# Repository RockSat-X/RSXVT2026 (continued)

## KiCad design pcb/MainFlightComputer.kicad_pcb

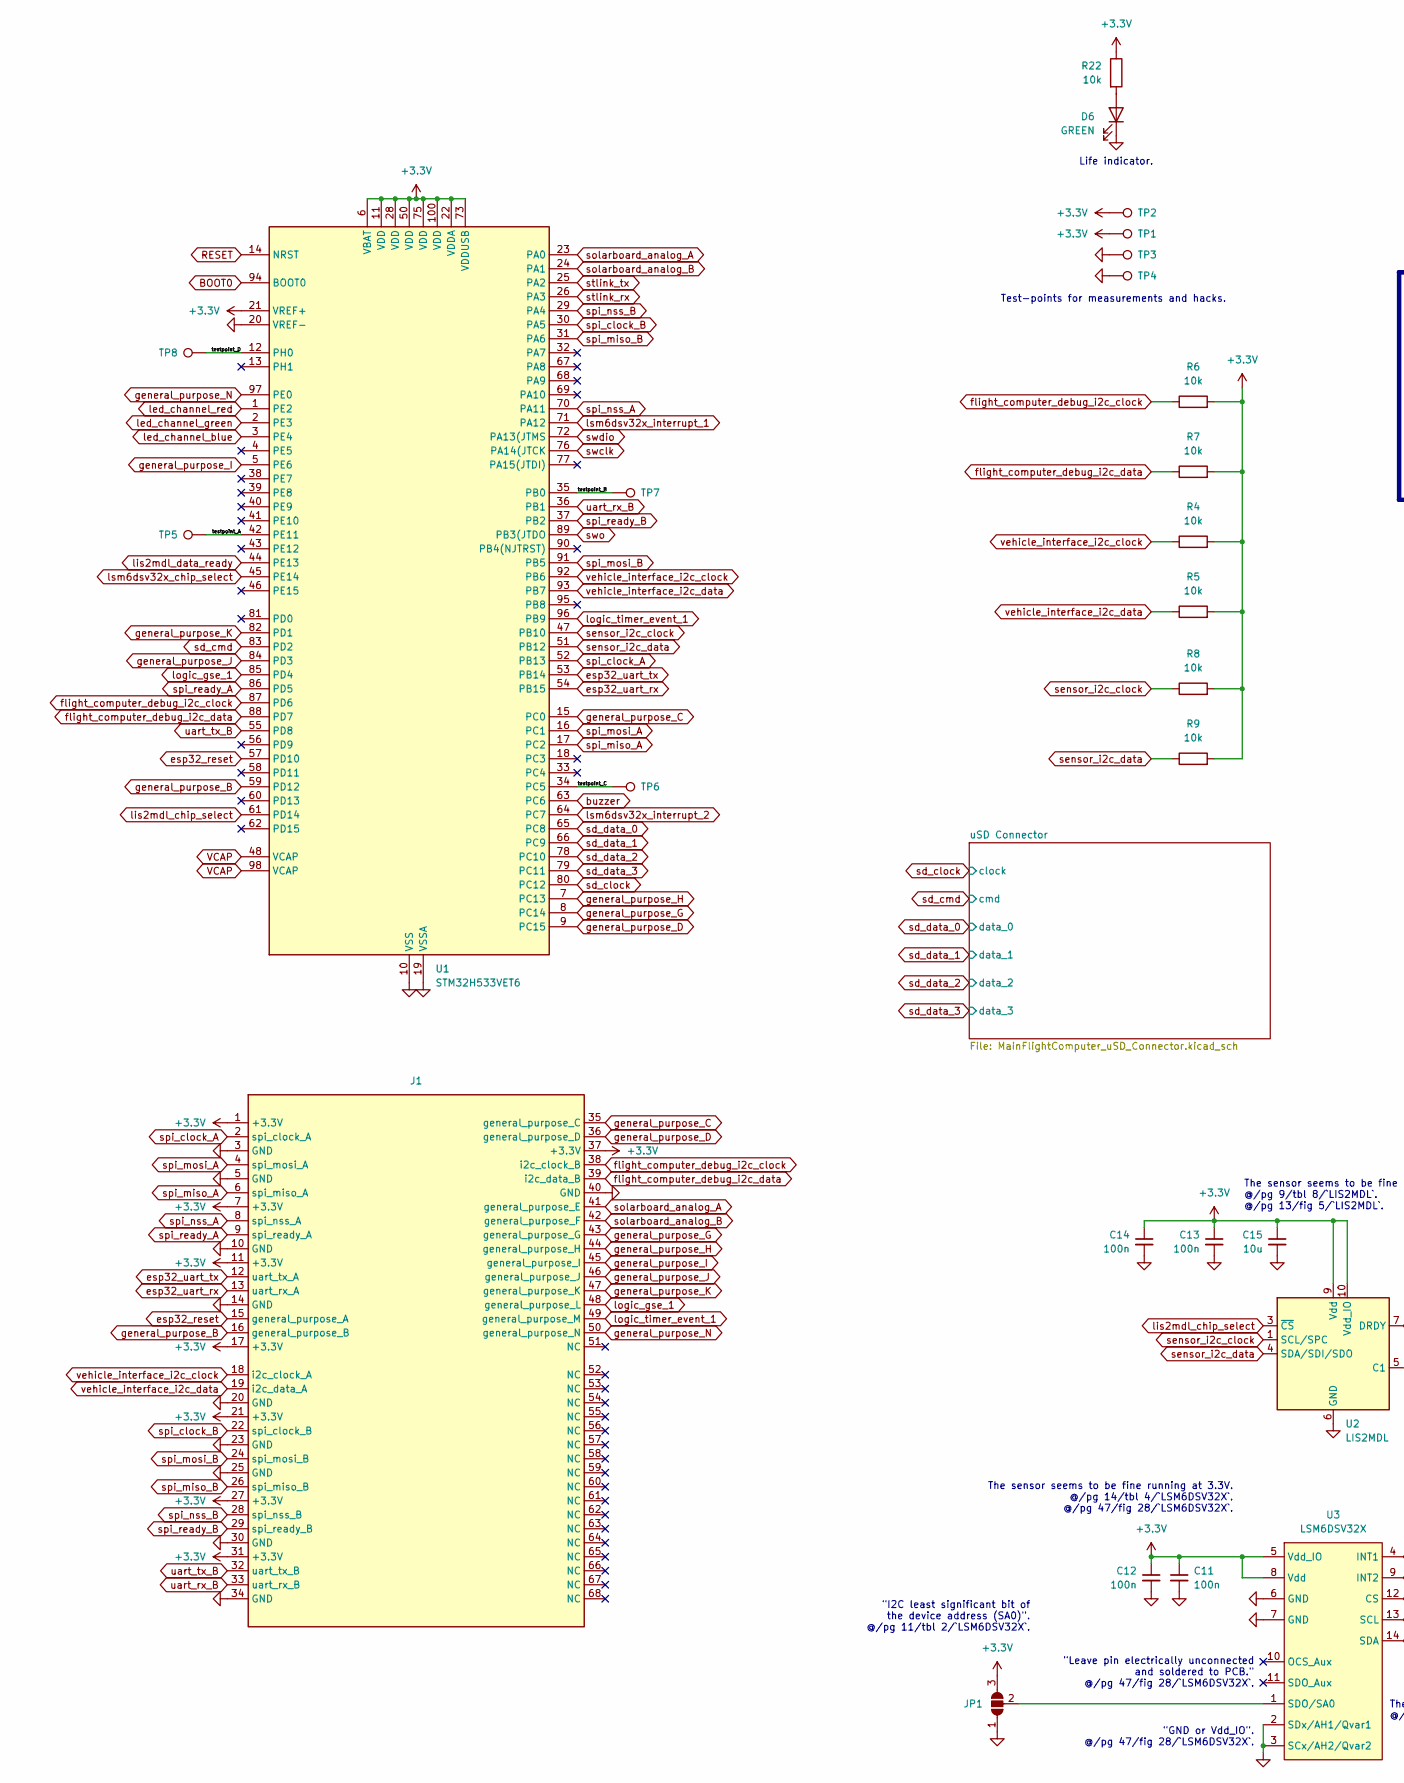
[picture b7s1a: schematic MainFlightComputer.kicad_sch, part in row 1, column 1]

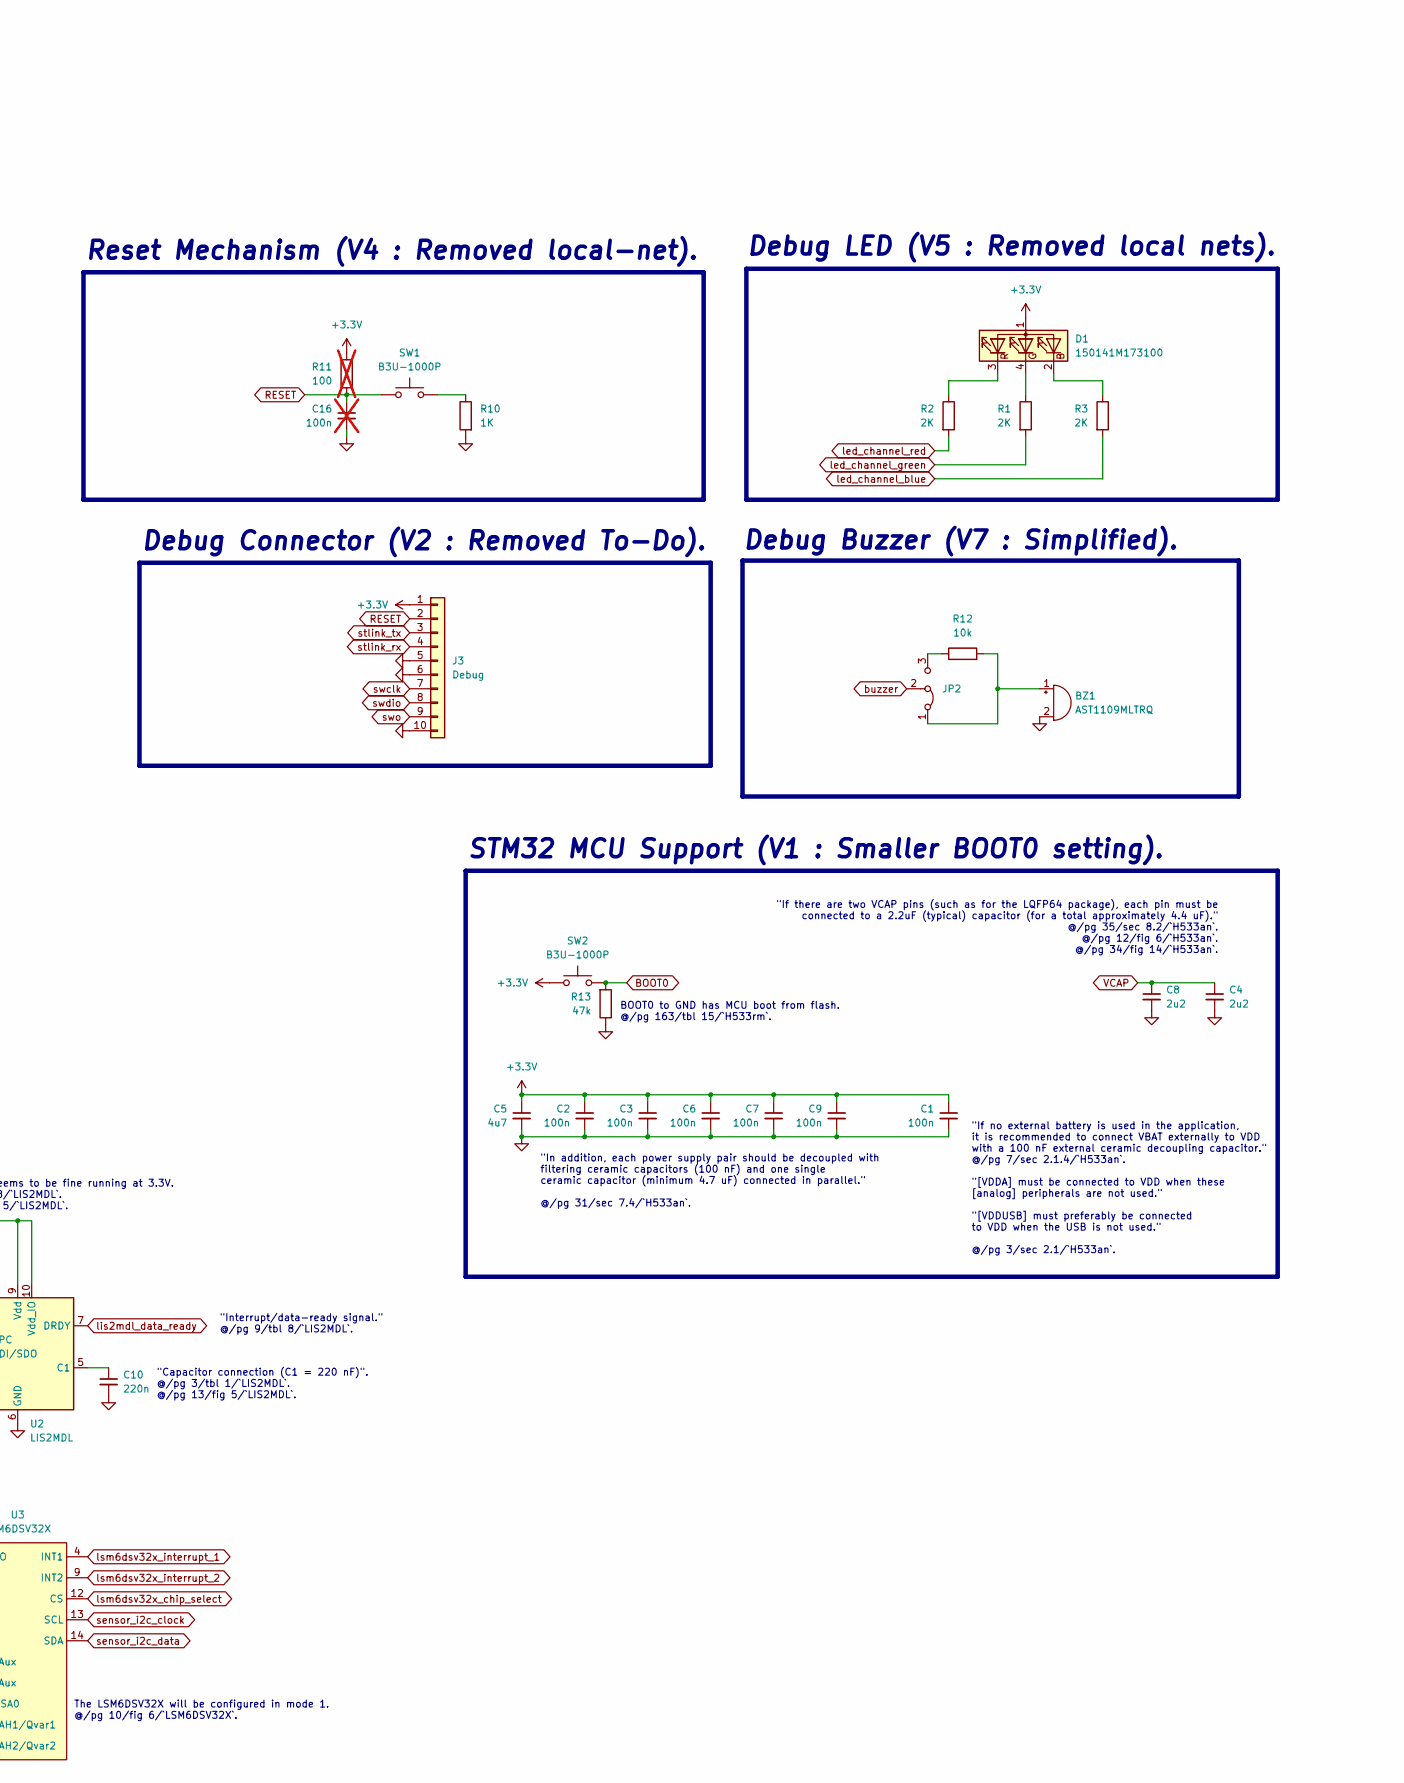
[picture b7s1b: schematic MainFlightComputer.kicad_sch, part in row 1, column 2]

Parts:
BZ1: AST1109MLTRQ; Buzzer_Mallory_AST1109MLTRQ
C1, C2, C3, C6, C7, C9, C11, C12, C13, C14: 100n; C_1206_3216Metric_Pad1.33x1.80mm_HandSolder
C4, C8: 2u2; C_1206_3216Metric_Pad1.33x1.80mm_HandSolder
C5: 4u7; C_1206_3216Metric_Pad1.33x1.80mm_HandSolder
C10: 220n; C_1206_3216Metric_Pad1.33x1.80mm_HandSolder
C15: 10u; C_1206_3216Metric_Pad1.33x1.80mm_HandSolder
C16: 100n; C_1206_3216Metric_Pad1.33x1.80mm_HandSolder; not fitted
D1: 150141M173100; LED_RGB_Wuerth-PLCC4_3.2x2.8mm_150141M173100
D6: GREEN; LED_1206_3216Metric_Pad1.42x1.75mm_HandSolder
J1: MainStackConnector
J3: Debug; Molex_PicoBlade_53047-1010_1x10_P1.25mm_Vertical
JP1: SolderJumper_3_Open; SolderJumper-3_P1.3mm_Open_RoundedPad1.0x1.5mm_NumberLabels
JP2: Jumper_3_Bridged12; PinHeader_1x03_P2.54mm_Vertical
R1, R2, R3: 2K; R_1206_3216Metric_Pad1.30x1.75mm_HandSolder
R4, R5, R6, R7, R8, R9, R12, R22: 10k; R_1206_3216Metric_Pad1.30x1.75mm_HandSolder
R10: 1K; R_1206_3216Metric_Pad1.30x1.75mm_HandSolder
R11: 100; R_1206_3216Metric_Pad1.30x1.75mm_HandSolder; not fitted
R13: 47k; R_1206_3216Metric_Pad1.30x1.75mm_HandSolder
SW1, SW2: B3U-1000P; SW_SPST_B3U-1000P
TP1, TP2, TP3, TP4, TP5, TP6, TP7, TP8: TestPoint; TestPoint_Bridge_Pitch2.0mm_Drill0.7mm
U1: STM32H533VET6; LQFP-100_14x14mm_P0.5mm
U2: LIS2MDL; LGA-12_2x2mm_P0.5mm
U3: LSM6DSV32X; LGA-14_3x2.5mm_P0.5mm_LayoutBorder3x4y

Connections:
+3.3V: C1.1, C2.1, C3.1, C5.1, C6.1, C7.1, C9.1, C11.1, C12.1, C13.1, C14.1, C15.1, D1.1 (A), J1.1 (+3.3V), J1.7 (+3.3V), J1.11 (+3.3V), J1.17 (+3.3V), J1.21 (+3.3V), J1.27 (+3.3V), J1.31 (+3.3V), J1.37 (+3.3V), J3.1, JP1.3 (B), R4.2, R5.2, R6.2, R7.2, R8.2, R9.2, R11.1, R22.1, SW2.1, TP1.1, TP2.1, U1.6 (VBAT), U1.11 (VDD), U1.21 (VREF+), U1.22 (VDDA), U1.28 (VDD), U1.50 (VDD), U1.73 (VDDUSB), U1.75 (VDD), U1.100 (VDD), U2.9 (Vdd), U2.10 (Vdd_IO), U3.5 (Vdd_IO), U3.8 (Vdd); also elsewhere on the board
/testpoint_A: TP5.1, U1.42 (PE11)
/testpoint_B: TP7.1, U1.35 (PB0)
/testpoint_C: TP6.1, U1.34 (PC5)
/testpoint_D: TP8.1, U1.12 (PH0)
BOOT0: R13.2, SW2.2, U1.94 (BOOT0)
GND: BZ1.2 (-), C1.2, C2.2, C3.2, C4.2, C5.2, C6.2, C7.2, C8.2, C9.2, C10.2, C11.2, C12.2, C13.2, C14.2, C15.2, C16.2, D6.1 (K), J1.3 (GND), J1.5 (GND), J1.10 (GND), J1.14 (GND), J1.20 (GND), J1.23 (GND), J1.25 (GND), J1.30 (GND), J1.34 (GND), J1.40 (GND), J3.5, J3.6, J3.10, JP1.1 (A), R10.2, R13.1, TP3.1, TP4.1, U1.10 (VSS), U1.19 (VSSA), U1.20 (VREF-), U1.27 (VSS), U1.49 (VSS), U1.74 (VSS), U1.99 (VSS), U2.6 (GND), U2.8 (GND), U3.2 (SDx/AH1/Qvar1), U3.3 (SCx/AH2/Qvar2), U3.6 (GND), U3.7 (GND); also elsewhere on the board
unnamed: BZ1.1 (+), JP2.1 (A), R12.2
unnamed: D1.2 (BK), R3.1
unnamed: D1.4 (GK), R1.1
unnamed: D1.3 (RK), R2.1
unnamed: D6.2 (A), R22.2
unnamed: JP1.2 (C), U3.1 (SDO/SA0)
unnamed: JP2.3 (B), R12.1
unnamed: R10.1, SW1.2
unnamed: C10.1, U2.5 (C1)
RESET: C16.1, J3.2, R11.2, SW1.1, U1.14 (NRST)
VCAP: C4.1, C8.1, U1.48 (VCAP), U1.98 (VCAP)
buzzer: JP2.2 (C), U1.63 (PC6)
esp32_reset: J1.15 (general_purpose_A), U1.57 (PD10)
esp32_uart_rx: J1.13 (uart_rx_A), U1.54 (PB15)
esp32_uart_tx: J1.12 (uart_tx_A), U1.53 (PB14)
flight_computer_debug_i2c_clock: J1.38 (i2c_clock_B), R6.1, U1.87 (PD6)
flight_computer_debug_i2c_data: J1.39 (i2c_data_B), R7.1, U1.88 (PD7)
general_purpose_B: J1.16 (general_purpose_B), U1.59 (PD12)
general_purpose_C: J1.35 (general_purpose_C), U1.15 (PC0)
general_purpose_D: J1.36 (general_purpose_D), U1.9 (PC15)
general_purpose_G: J1.43 (general_purpose_G), U1.8 (PC14)
general_purpose_H: J1.44 (general_purpose_H), U1.7 (PC13)
general_purpose_I: J1.45 (general_purpose_I), U1.5 (PE6)
general_purpose_J: J1.46 (general_purpose_J), U1.84 (PD3)
general_purpose_K: J1.47 (general_purpose_K), U1.82 (PD1)
general_purpose_N: J1.50 (general_purpose_N), U1.97 (PE0)
led_channel_blue: R3.2, U1.3 (PE4)
led_channel_green: R1.2, U1.2 (PE3)
led_channel_red: R2.2, U1.1 (PE2)
lis2mdl_chip_select: U1.61 (PD14), U2.3 (~CS)
lis2mdl_data_ready: U1.44 (PE13), U2.7 (DRDY)
logic_gse_1: J1.48 (general_purpose_L), U1.85 (PD4)
logic_timer_event_1: J1.49 (general_purpose_M), U1.96 (PB9)
lsm6dsv32x_chip_select: U1.45 (PE14), U3.12 (CS)
lsm6dsv32x_interrupt_1: U1.71 (PA12), U3.4 (INT1)
lsm6dsv32x_interrupt_2: U1.64 (PC7), U3.9 (INT2)
sd_clock: U1.80 (PC12); also elsewhere on the board
sd_cmd: U1.83 (PD2); also elsewhere on the board
sd_data_0: U1.65 (PC8); also elsewhere on the board
sd_data_1: U1.66 (PC9); also elsewhere on the board
sd_data_2: U1.78 (PC10); also elsewhere on the board
sd_data_3: U1.79 (PC11); also elsewhere on the board
sensor_i2c_clock: R8.1, U1.47 (PB10), U2.1 (SCL/SPC), U3.13 (SCL)
sensor_i2c_data: R9.1, U1.51 (PB12), U2.4 (SDA/SDI/SDO), U3.14 (SDA)
solarboard_analog_A: J1.41 (general_purpose_E), U1.23 (PA0)
solarboard_analog_B: J1.42 (general_purpose_F), U1.24 (PA1)
spi_clock_A: J1.2 (spi_clock_A), U1.52 (PB13)
spi_clock_B: J1.22 (spi_clock_B), U1.30 (PA5)
spi_miso_A: J1.6 (spi_miso_A), U1.17 (PC2)
spi_miso_B: J1.26 (spi_miso_B), U1.31 (PA6)
spi_mosi_A: J1.4 (spi_mosi_A), U1.16 (PC1)
spi_mosi_B: J1.24 (spi_mosi_B), U1.91 (PB5)
spi_nss_A: J1.8 (spi_nss_A), U1.70 (PA11)
spi_nss_B: J1.28 (spi_nss_B), U1.29 (PA4)
spi_ready_A: J1.9 (spi_ready_A), U1.86 (PD5)
spi_ready_B: J1.29 (spi_ready_B), U1.37 (PB2)
stlink_rx: J3.4, U1.26 (PA3)
stlink_tx: J3.3, U1.25 (PA2)
swclk: J3.7, U1.76 (PA14(JTCK)
swdio: J3.8, U1.72 (PA13(JTMS)
swo: J3.9, U1.89 (PB3(JTDO)
uart_rx_B: J1.33 (uart_rx_B), U1.36 (PB1)
uart_tx_B: J1.32 (uart_tx_B), U1.55 (PD8)
vehicle_interface_i2c_clock: J1.18 (i2c_clock_A), R4.1, U1.92 (PB6)
vehicle_interface_i2c_data: J1.19 (i2c_data_A), R5.1, U1.93 (PB7)

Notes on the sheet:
STM32 MCU Support (V1 : Smaller BOOT0 setting).
Life indicator.
"Interrupt/data-ready signal." @/pg 9/tbl 8/`LIS2MDL`.
Reset Mechanism (V4 : Removed local-net).
The sensor seems to be fine running at 3.3V. @/pg 14/tbl 4/`LSM6DSV32X`. @/pg 47/fig 28/`LSM6DSV32X`.
Debug Connector (V2 : Removed To-Do).
The sensor seems to be fine running at 3.3V. @/pg 9/tbl 8/`LIS2MDL`. @/pg 13/fig 5/`LIS2MDL`.
Test-points for measurements and hacks.
BOOT0 to GND has MCU boot from flash. @/pg 163/tbl 15/`H533rm`.
"GND or Vdd_IO". @/pg 47/fig 28/`LSM6DSV32X`.
"If there are two VCAP pins (such as for the LQFP64 package), each pin must be connected to a 2.2uF (typical) capacitor (for a total approximately 4.4 uF)." @/pg 35/sec 8.2/`H533an`. @/pg 12/fig 6/`H533an`. @/pg 34/fig 14/`H533an`.
The LSM6DSV32X will be configured in mode 1. @/pg 10/fig 6/`LSM6DSV32X`.
"Capacitor connection (C1 = 220 nF)". @/pg 3/tbl 1/`LIS2MDL`. @/pg 13/fig 5/`LIS2MDL`.
"Leave pin electrically unconnected and soldered to PCB." @/pg 47/fig 28/`LSM6DSV32X`.
"In addition, each power supply pair should be decoupled with filtering ceramic capacitors (100 nF) and one single ceramic capacitor (minimum 4.7 uF) connected in parallel." @/pg 31/sec 7.4/`H533an`.
"If no external battery is used in the application, it is recommended to connect VBAT externally to VDD with a 100 nF external ceramic decoupling capacitor." @/pg 7/sec 2.1.4/`H533an`. "[VDDA] must be connected to VDD when these [analog] peripherals are not used." "[VDDUSB] must preferably be conne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
Debug Buzzer (V7 : Simplified).
Debug LED (V5 : Removed local nets).
"I2C least significant bit of the device address (SA0)". @/pg 11/tbl 2/`LSM6DSV32X`.

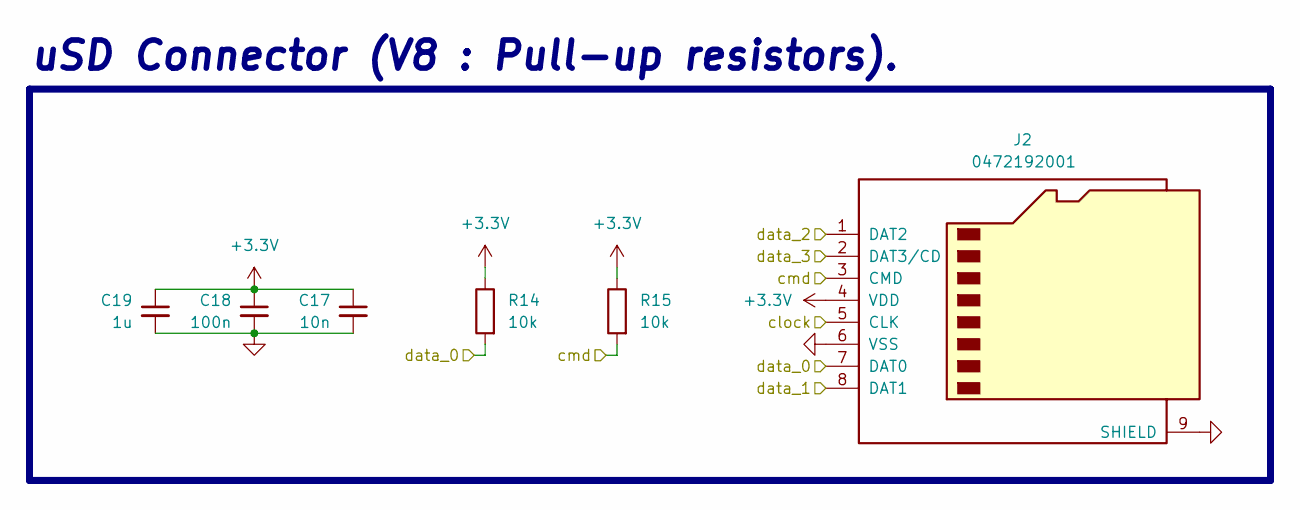
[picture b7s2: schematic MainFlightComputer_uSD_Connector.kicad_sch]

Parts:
C17: 10n; C_1206_3216Metric_Pad1.33x1.80mm_HandSolder
C18: 100n; C_1206_3216Metric_Pad1.33x1.80mm_HandSolder
C19: 1u; C_1206_3216Metric_Pad1.33x1.80mm_HandSolder
J2: 0472192001; microSD_HC_Molex_47219-2001
R14, R15: 10k; R_1206_3216Metric_Pad1.30x1.75mm_HandSolder

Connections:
+3.3V: C17.1, C18.1, C19.1, J2.4 (VDD), R14.1, R15.1; also elsewhere on the board
GND: C17.2, C18.2, C19.2, J2.6 (VSS), J2.9 (SHIELD); also elsewhere on the board
sd_clock: J2.5 (CLK); also elsewhere on the board
sd_cmd: J2.3 (CMD), R15.2; also elsewhere on the board
sd_data_0: J2.7 (DAT0), R14.2; also elsewhere on the board
sd_data_1: J2.8 (DAT1); also elsewhere on the board
sd_data_2: J2.1 (DAT2); also elsewhere on the board
sd_data_3: J2.2 (DAT3/CD); also elsewhere on the board

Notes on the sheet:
uSD Connector (V8 : Pull-up resistors).

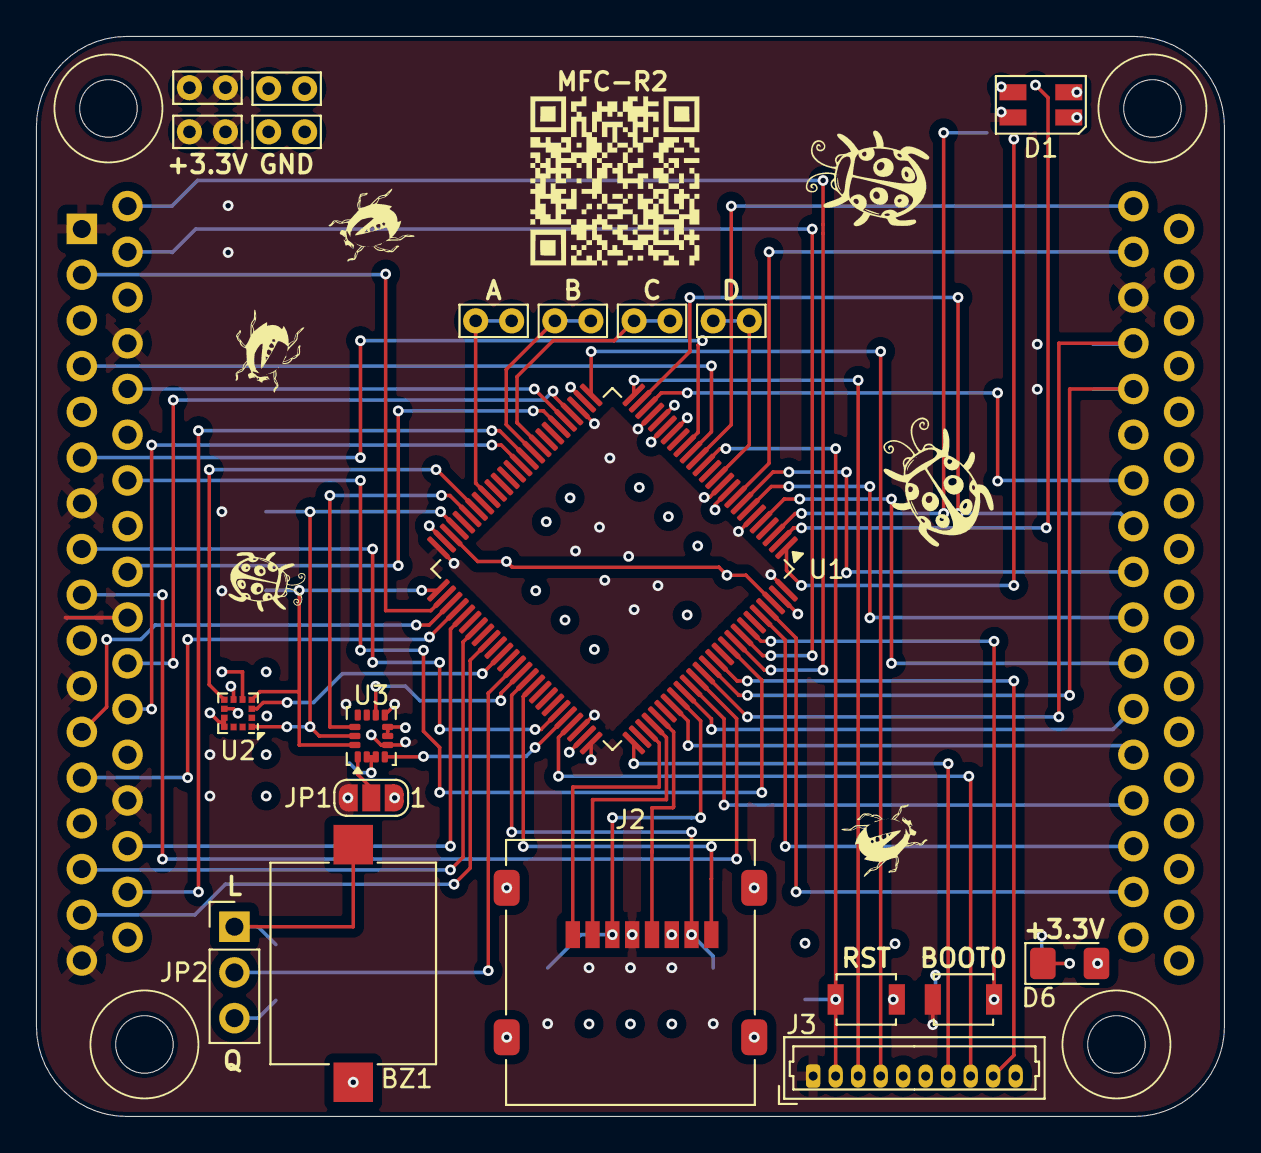
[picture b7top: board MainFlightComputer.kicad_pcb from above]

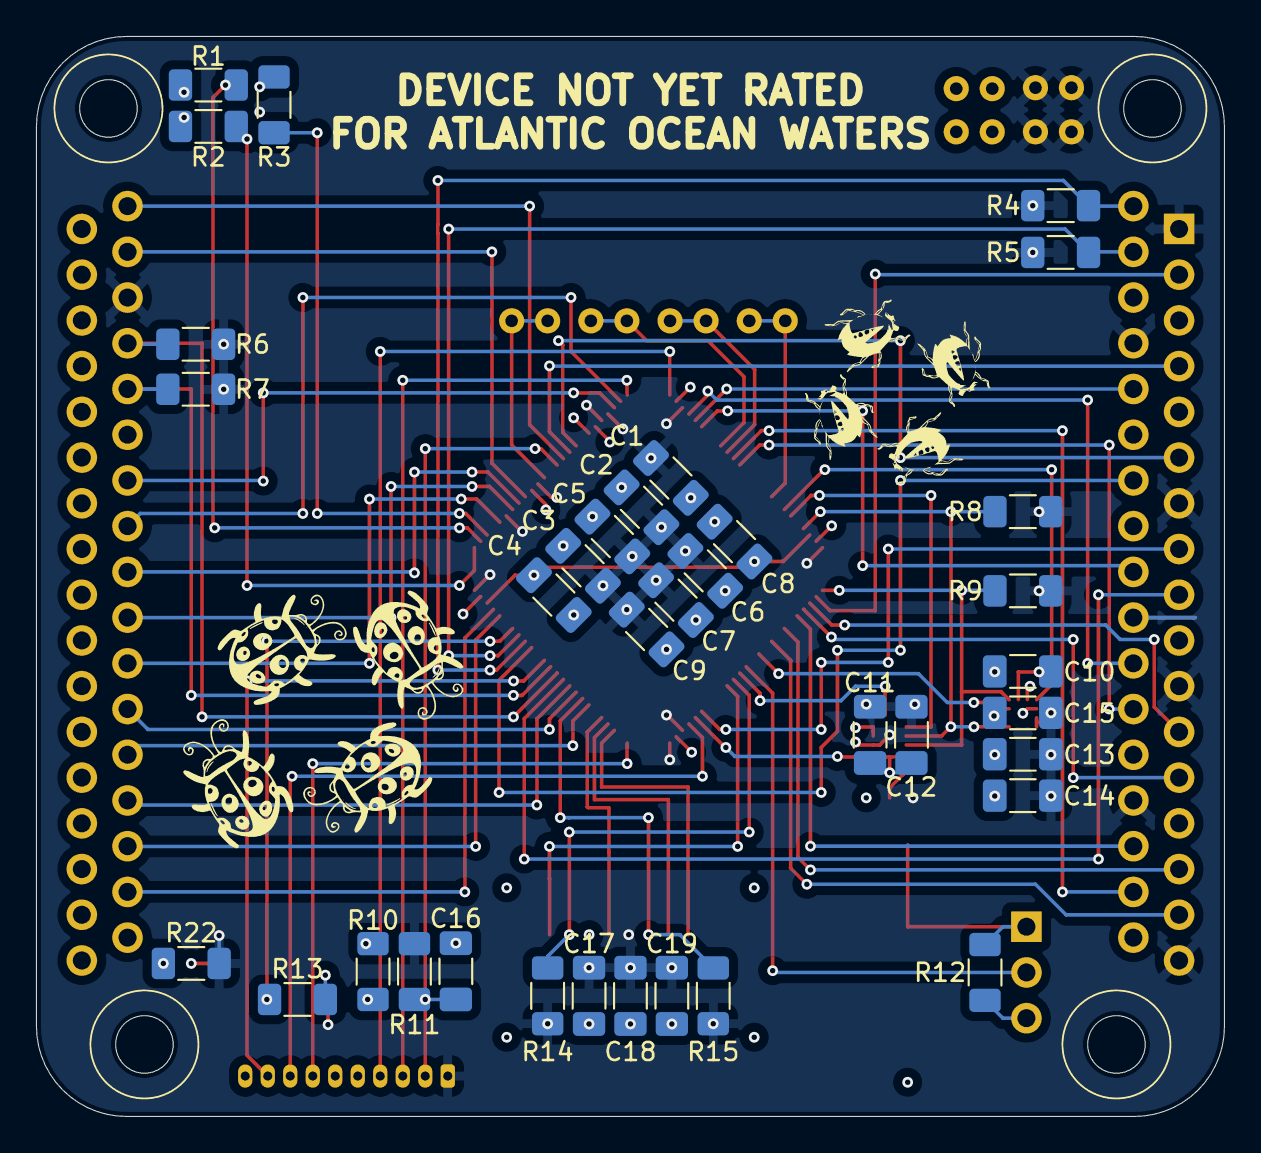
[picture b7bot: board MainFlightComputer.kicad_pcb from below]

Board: 4 copper layers, 66.0 x 60.0 mm, 57 parts (35 on the bottom side), 72 nets.

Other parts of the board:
N1: Housing; MainFlightComputerHousing

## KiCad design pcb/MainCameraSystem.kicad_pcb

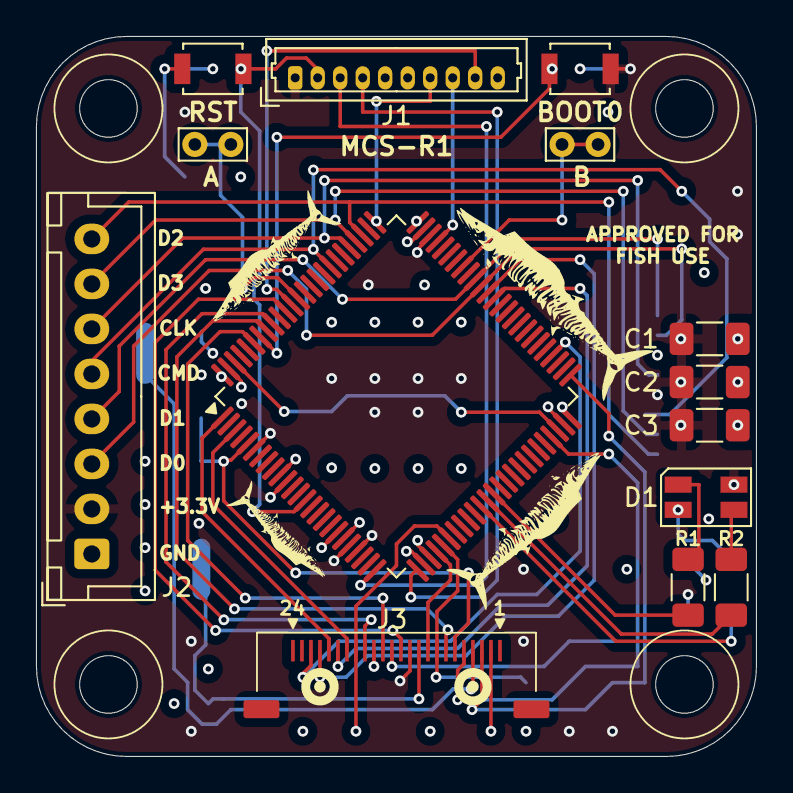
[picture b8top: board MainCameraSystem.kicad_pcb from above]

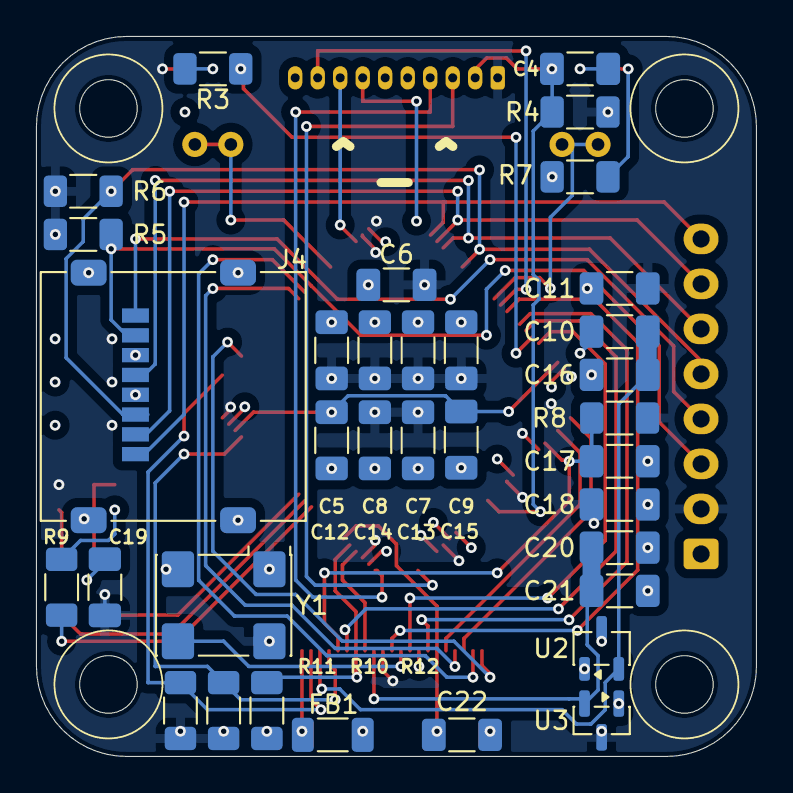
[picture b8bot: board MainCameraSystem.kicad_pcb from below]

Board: 4 copper layers, 40.0 x 40.0 mm, 52 parts (34 on the bottom side), 44 nets.

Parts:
C1, C16, C18, C20: 1u; C_1206_3216Metric_Pad1.33x1.80mm_HandSolder
C2, C4, C5, C6, C7, C8, C13, C14, C17: 100n; C_1206_3216Metric_Pad1.33x1.80mm_HandSolder
C3, C19: 10n; C_1206_3216Metric_Pad1.33x1.80mm_HandSolder
C9: 4u7; C_1206_3216Metric_Pad1.33x1.80mm_HandSolder
C10, C11, C21: 10u; C_1206_3216Metric_Pad1.33x1.80mm_HandSolder
C12, C15: 2u2; C_1206_3216Metric_Pad1.33x1.80mm_HandSolder
C22: 22p; C_1206_3216Metric_Pad1.33x1.80mm_HandSolder
D1: 150141M173100; LED_RGB_Wuerth-PLCC4_3.2x2.8mm_150141M173100
FB1: Ferrite; L_1206_3216Metric_Pad1.22x1.90mm_HandSolder
H1, H2, H3, H4: MountingHole; MountingHole_3.2mm_M3
J1: Debug; Molex_PicoBlade_53047-1010_1x10_P1.25mm_Vertical
J2: B8B-XH-A; JST_XH_B8B-XH-A_1x08_P2.50mm_Vertical
J3: XF3M_2415_1B; XF3M_2415_1B - REVERSED
J4: 0472192001; microSD_HC_Molex_47219-2001
R1, R2, R9: 2K; R_1206_3216Metric_Pad1.30x1.75mm_HandSolder
R3: 47k; R_1206_3216Metric_Pad1.30x1.75mm_HandSolder
R4: 100; R_1206_3216Metric_Pad1.30x1.75mm_HandSolder
R5, R6, R8, R10, R11, R12: 10k; R_1206_3216Metric_Pad1.30x1.75mm_HandSolder
R7: 1K; R_1206_3216Metric_Pad1.30x1.75mm_HandSolder
SW1, SW2: B3U-1000P; SW_SPST_B3U-1000P
TP1, TP2: TestPoint; TestPoint_Bridge_Pitch2.0mm_Drill0.7mm
U1: STM32H533VET6; LQFP-100_14x14mm_P0.5mm
U2: AP2127N-2.8TRG1; SOT-23-3
U3: AP2127N-1.5TRG1; SOT-23
Y1: ASV-24.000MHZ-EJ-T; Oscillator_SMD_Abracon_ASV-4Pin_7.0x5.1mm

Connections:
+1V5: C20.1, C21.1, J3.10, U3.2 (VO)
+2V8: C10.1, C16.1, J3.4, U2.2 (VO)
+3.3V: C1.1, C2.1, C3.1, C5.1, C6.1, C7.1, C8.1, C9.1, C11.1, C13.1, C14.1, C18.1, C19.1, D1.1 (A), J1.1, J2.2, J3.11, J4.4 (VDD), R4.1, R5.1, R6.1, R8.1, R10.1, R11.1, SW2.1, U1.6 (VBAT), U1.11 (VDD), U1.21 (VREF+), U1.22 (VDDA), U1.28 (VDD), U1.50 (VDD), U1.73 (VDDUSB), U1.75 (VDD), U1.100 (VDD), U2.3 (VI), U3.3 (VI), Y1.1 (EN), Y1.4 (Vdd)
/testpoint_A: TP1.1, U1.88 (PD7)
/testpoint_B: TP2.1, U1.68 (PA9)
BOOT0: R3.2, SW2.2, U1.94 (BOOT0)
GND: C1.2, C2.2, C3.2, C4.2, C5.2, C6.2, C7.2, C8.2, C9.2, C10.2, C11.2, C12.2, C13.2, C14.2, C15.2, C16.2, C17.2, C18.2, C19.2, C20.2, C21.2, C22.2, FB1.1, J1.5, J1.6, J1.10, J2.1, J3.15, J4.6 (VSS), J4.9 (SHIELD), R3.1, R7.2, R12.2, U1.10 (VSS), U1.19 (VSSA), U1.20 (VREF-), U1.27 (VSS), U1.49 (VSS), U1.74 (VSS), U1.99 (VSS), U2.1 (GND), U3.1 (GND), Y1.2 (GND)
GNDA: FB1.2, J3.2
unnamed: D1.2 (BK), R2.1
unnamed: D1.4 (GK), R9.1
unnamed: D1.3 (RK), R1.1
unnamed: R7.1, SW1.2
OV_XCLK: J3.13, Y1.3 (OUT)
RESET: C4.1, J1.2, R4.2, SW1.1, U1.14 (NRST)
VCAP: C12.1, C15.1, U1.48 (VCAP), U1.98 (VCAP)
led_channel_blue: R2.2, U1.37 (PB2)
led_channel_green: R9.2, U1.36 (PB1)
led_channel_red: R1.2, U1.38 (PE7)
ovcam_hsync: J3.9, U1.29 (PA4)
ovcam_i2c_clock: J3.5, R10.2, U1.47 (PB10)
ovcam_i2c_data: J3.3, R11.2, U1.51 (PB12)
ovcam_pixel_clock: C22.1, J3.17, U1.31 (PA6)
ovcam_power_down: J3.8, R12.1, U1.30 (PA5)
ovcam_reset: C17.1, J3.6, R8.2, U1.5 (PE6)
ovcam_vsync: J3.7, U1.93 (PB7)
ovcam_y2: J3.19, U1.63 (PC6)
ovcam_y3: J3.21, U1.64 (PC7)
ovcam_y4: J3.22, U1.54 (PB15)
ovcam_y5: J3.20, U1.1 (PE2)
ovcam_y6: J3.18, U1.3 (PE4)
ovcam_y7: J3.16, U1.92 (PB6)
ovcam_y8: J3.14, U1.95 (PB8)
ovcam_y9: J3.12, U1.90 (PB4(NJTRST))
sd_clock: J2.6, J4.5 (CLK), U1.80 (PC12)
sd_cmd: J2.5, J4.3 (CMD), R6.2, U1.83 (PD2)
sd_data_0: J2.3, J4.7 (DAT0), R5.2, U1.65 (PC8)
sd_data_1: J2.4, J4.8 (DAT1), U1.66 (PC9)
sd_data_2: J2.8, J4.1 (DAT2), U1.78 (PC10)
sd_data_3: J2.7, J4.2 (DAT3/CD), U1.79 (PC11)
stlink_rx: J1.4, U1.26 (PA3)
stlink_tx: J1.3, U1.25 (PA2)
swclk: J1.7, U1.76 (PA14(JTCK)
swdio: J1.8, U1.72 (PA13(JTMS)
swo: J1.9, U1.89 (PB3(JTDO)

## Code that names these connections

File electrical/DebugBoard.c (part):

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    for (i32 i = 0; i < 32; i += 1)
    {

        GPIO_ACTIVE  (led_channel_red_A  );
        GPIO_INACTIVE(led_channel_green_A);
        GPIO_INACTIVE(led_channel_blue_A );
        GPIO_ACTIVE  (led_channel_red_B  );
        GPIO_INACTIVE(led_channel_green_B);
        GPIO_INACTIVE(led_channel_blue_B );
        GPIO_ACTIVE  (led_channel_red_C  );
        GPIO_INACTIVE(led_channel_green_C);
        GPIO_INACTIVE(led_channel_blue_C );
        GPIO_ACTIVE  (led_channel_red_D  );
        GPIO_INACTIVE(led_channel_green_D);
        GPIO_INACTIVE(led_channel_blue_D );
        spinlock_us(50'000);

        GPIO_INACTIVE(led_channel_red_A  );
        GPIO_INACTIVE(led_channel_green_A);
        GPIO_INACTIVE(led_channel_blue_A );
        GPIO_INACTIVE(led_channel_red_B  );
        GPIO_INACTIVE(led_channel_green_B);
        GPIO_INACTIVE(led_channel_blue_B );
        GPIO_INACTIVE(led_channel_red_C  );
        GPIO_INACTIVE(led_channel_green_C);
        GPIO_INACTIVE(led_channel_blue_C );
        GPIO_INACTIVE(led_channel_red_D  );
        GPIO_INACTIVE(led_channel_green_D);
        GPIO_INACTIVE(led_channel_blue_D );
        spinlock_us(50'000);

    }
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        if (havent_received_a_packet_in_a_while && !BUZZER_current_tune())
        {
            BUZZER_play(BuzzerTune_hazard);
            GPIO_TOGGLE  (led_channel_red_C  );
            GPIO_INACTIVE(led_channel_green_C);
            GPIO_INACTIVE(led_channel_blue_C );
        }


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            {
                condition = "???";

                GPIO_ACTIVE(led_channel_red_B  );
                GPIO_ACTIVE(led_channel_green_B);
                GPIO_ACTIVE(led_channel_blue_B );

            }
            else
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                BUZZER_play(BuzzerTune_deep_beep);
            }

            GPIO_ACTIVE  (led_channel_red_B  );
            GPIO_INACTIVE(led_channel_green_B);
            GPIO_INACTIVE(led_channel_blue_B );

        }
        else
        {
            GPIO_INACTIVE(led_channel_red_B  );
            GPIO_ACTIVE  (led_channel_green_B);
            GPIO_INACTIVE(led_channel_blue_B );
        }

        if (TIMEKEEPING_microseconds() - status_flag_timestamp_us >= 1'000'000) // Scroll the statuses slowly over time.
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        if (completely_wipe_filesystem)
        {
            BUZZER_play(BuzzerTune_tetris);
            GPIO_ACTIVE(led_channel_red_D  );
            GPIO_ACTIVE(led_channel_green_D);
            GPIO_ACTIVE(led_channel_blue_D );
        }
        else
        {
            GPIO_ACTIVE  (led_channel_red_D  );
            GPIO_INACTIVE(led_channel_green_D);
            GPIO_ACTIVE  (led_channel_blue_D );
        }


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
        completely_wipe_filesystem = false;

        GPIO_INACTIVE(led_channel_red_D  );
        GPIO_INACTIVE(led_channel_green_D);
        GPIO_INACTIVE(led_channel_blue_D );

        switch (reinit_result)
        {
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
            case FileSystemReinitResult_success:
            {
                GPIO_INACTIVE(led_channel_red_D  );
                GPIO_ACTIVE  (led_channel_green_D);
                GPIO_INACTIVE(led_channel_blue_D );
            } break;


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
                for (i32 i = 0; i < 32; i += 1)
                {
                    GPIO_TOGGLE  (led_channel_red_D  );
                    GPIO_INACTIVE(led_channel_green_D);
                    GPIO_TOGGLE  (led_channel_blue_D );
                    FREERTOS_delay_ms(25);
                }

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
                for (i32 i = 0; i < 128; i += 1)
                {
                    GPIO_TOGGLE(led_channel_red_D  );
                    GPIO_TOGGLE(led_channel_green_D);
                    GPIO_TOGGLE(led_channel_blue_D );
                    FREERTOS_delay_ms(25);
                }

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
                    case FileSystemSaveResult_success:
                    {
                        GPIO_INACTIVE(led_channel_red_D  );
                        GPIO_TOGGLE  (led_channel_green_D);
                        GPIO_INACTIVE(led_channel_blue_D );
                    } break;


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        while (BUZZER_current_tune())
        {

            GPIO_ACTIVE  (led_channel_red_A  );
            GPIO_INACTIVE(led_channel_green_A);
            GPIO_INACTIVE(led_channel_blue_A );
            FREERTOS_delay_ms(20);

            GPIO_ACTIVE  (led_channel_red_A  );
            GPIO_ACTIVE  (led_channel_green_A);
            GPIO_INACTIVE(led_channel_blue_A );
            FREERTOS_delay_ms(20);

            GPIO_INACTIVE(led_channel_red_A  );
            GPIO_ACTIVE  (led_channel_green_A);
            GPIO_INACTIVE(led_channel_blue_A );
            FREERTOS_delay_ms(20);

            GPIO_INACTIVE(led_channel_red_A  );
            GPIO_ACTIVE  (led_channel_green_A);
            GPIO_ACTIVE  (led_channel_blue_A );
            FREERTOS_delay_ms(20);

            GPIO_INACTIVE(led_channel_red_A  );
            GPIO_INACTIVE(led_channel_green_A);
            GPIO_ACTIVE  (led_channel_blue_A );
            FREERTOS_delay_ms(20);

            GPIO_ACTIVE  (led_channel_red_A  );
            GPIO_INACTIVE(led_channel_green_A);
            GPIO_ACTIVE  (led_channel_blue_A );
            FREERTOS_delay_ms(20);

        }

        GPIO_INACTIVE(led_channel_red_A  );
        GPIO_INACTIVE(led_channel_green_A);
        GPIO_INACTIVE(led_channel_blue_A );

        FREERTOS_delay_ms(100);

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
                if (digest) // Checksum mismatch?
                {
                    GPIO_ACTIVE  (led_channel_red_C  );
                    GPIO_INACTIVE(led_channel_green_C);
                    GPIO_INACTIVE(led_channel_blue_C );
                }
                else
                {
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                        // Ring-buffer full! Should be fine though...
                    }

                    GPIO_INACTIVE(led_channel_red_C  );
                    GPIO_TOGGLE  (led_channel_green_C);
                    GPIO_INACTIVE(led_channel_blue_C );

                }

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
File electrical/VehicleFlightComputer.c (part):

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
    while (BUZZER_current_tune());

    GPIO_ACTIVE(battery_allowed);



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
        enum DiagnosticMask current_diagnostic = current_flags & -current_flags;

        GPIO_INACTIVE(led_channel_red  );
        GPIO_INACTIVE(led_channel_green);
        GPIO_INACTIVE(led_channel_blue );

        if (current_diagnostic && __builtin_ctz(current_diagnostic) < countof(DIAGNOSTIC_TABLE))
        {
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
                switch (info->behavior_red)
                {
                    case DiagnosticLEDBehavior_inactive : GPIO_INACTIVE(led_channel_red); break;
                    case DiagnosticLEDBehavior_active   : GPIO_ACTIVE  (led_channel_red); break;
                    case DiagnosticLEDBehavior_toggle   : GPIO_TOGGLE  (led_channel_red); break;
                    default                             : sus;
                }

                switch (info->behavior_green)
                {
                    case DiagnosticLEDBehavior_inactive : GPIO_INACTIVE(led_channel_green); break;
                    case DiagnosticLEDBehavior_active   : GPIO_ACTIVE  (led_channel_green); break;
                    case DiagnosticLEDBehavior_toggle   : GPIO_TOGGLE  (led_channel_green); break;
                    default                             : sus;
                }

                switch (info->behavior_blue)
                {
                    case DiagnosticLEDBehavior_inactive : GPIO_INACTIVE(led_channel_blue); break;
                    case DiagnosticLEDBehavior_active   : GPIO_ACTIVE  (led_channel_blue); break;
                    case DiagnosticLEDBehavior_toggle   : GPIO_TOGGLE  (led_channel_blue); break;
                    default                             : sus;
                }

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            sus; // Invalid diagnostic..?
        }

        GPIO_INACTIVE(led_channel_red  );
        GPIO_INACTIVE(led_channel_green);
        GPIO_INACTIVE(led_channel_blue );

        current_flags &= ~current_diagnostic; // Acknowledge the completion of the diagnostic.

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                memory_order_relaxed // No synchronization needed.
            );

        b32 theres_still_external_power             = GPIO_READ(external_detected);
        b32 vehicle_interface_currently_pulled_down = !GPIO_READ(vehicle_interface_i2c_clock) && !GPIO_READ(vehicle_interface_i2c_data);

        if (!vehicle_interface_currently_pulled_down)
        {
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
            // Try cut off battery power.

            GPIO_INACTIVE(battery_allowed);
            spinlock_us(1'000'000);


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
        // Reset the OpenMV for a bit...

        GPIO_ACTIVE(openmv_reset);
        FREERTOS_delay_ms(10);


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        // Reawaken the OpenMV!

        FREERTOS_delay_ms(10);
        GPIO_INACTIVE(openmv_reset);



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
        // Reset the ESP32 for a bit...

        GPIO_ACTIVE(esp32_reset);
        FREERTOS_delay_ms(10);


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        // Reawaken the ESP32!

        FREERTOS_delay_ms(10);
        GPIO_INACTIVE(esp32_reset);



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                    vn100_packet_exist ? vn100_packet_data.GyroX  : NAN,
                    vn100_packet_exist ? vn100_packet_data.GyroY  : NAN,
                    vn100_packet_exist ? vn100_packet_data.GyroZ  : NAN,
                    GPIO_READ(external_detected)          ? "Yes" : "No",
                    VN100.magnetic_disturbance_exists     ? "Yes" : "No",
                    VN100.acceleration_disturbance_exists ? "Yes" : "No",
                    openmv_gnc_packet_exist ? openmv_gnc_packet_data.attitude_yaw                       : NAN,
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
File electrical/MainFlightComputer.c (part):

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    for (i32 i = 0; i < 8; i += 1)
    {

        GPIO_ACTIVE  (led_channel_red  );
        GPIO_INACTIVE(led_channel_green);
        GPIO_INACTIVE(led_channel_blue );
        spinlock_us(20'000);

        GPIO_ACTIVE  (led_channel_red  );
        GPIO_ACTIVE  (led_channel_green);
        GPIO_INACTIVE(led_channel_blue );
        spinlock_us(20'000);

        GPIO_INACTIVE(led_channel_red  );
        GPIO_ACTIVE  (led_channel_green);
        GPIO_INACTIVE(led_channel_blue );
        spinlock_us(20'000);

        GPIO_INACTIVE(led_channel_red  );
        GPIO_ACTIVE  (led_channel_green);
        GPIO_ACTIVE  (led_channel_blue );
        spinlock_us(20'000);

        GPIO_INACTIVE(led_channel_red  );
        GPIO_INACTIVE(led_channel_green);
        GPIO_ACTIVE  (led_channel_blue );
        spinlock_us(20'000);

        GPIO_ACTIVE  (led_channel_red  );
        GPIO_INACTIVE(led_channel_green);
        GPIO_ACTIVE  (led_channel_blue );
        spinlock_us(20'000);

    }

    GPIO_INACTIVE(led_channel_red  );
    GPIO_INACTIVE(led_channel_green);
    GPIO_INACTIVE(led_channel_blue );



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
        enum DiagnosticMask current_diagnostic = current_flags & -current_flags;

        GPIO_INACTIVE(led_channel_red  );
        GPIO_INACTIVE(led_channel_green);
        GPIO_INACTIVE(led_channel_blue );

        if (current_diagnostic && __builtin_ctz(current_diagnostic) < countof(DIAGNOSTIC_TABLE))
        {
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
                switch (info->behavior_red)
                {
                    case DiagnosticLEDBehavior_inactive : GPIO_INACTIVE(led_channel_red); break;
                    case DiagnosticLEDBehavior_active   : GPIO_ACTIVE  (led_channel_red); break;
                    case DiagnosticLEDBehavior_toggle   : GPIO_TOGGLE  (led_channel_red); break;
                    default                             : sus;
                }

                switch (info->behavior_green)
                {
                    case DiagnosticLEDBehavior_inactive : GPIO_INACTIVE(led_channel_green); break;
                    case DiagnosticLEDBehavior_active   : GPIO_ACTIVE  (led_channel_green); break;
                    case DiagnosticLEDBehavior_toggle   : GPIO_TOGGLE  (led_channel_green); break;
                    default                             : sus;
                }

                switch (info->behavior_blue)
                {
                    case DiagnosticLEDBehavior_inactive : GPIO_INACTIVE(led_channel_blue); break;
                    case DiagnosticLEDBehavior_active   : GPIO_ACTIVE  (led_channel_blue); break;
                    case DiagnosticLEDBehavior_toggle   : GPIO_TOGGLE  (led_channel_blue); break;
                    default                             : sus;
                }

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            sus; // Invalid diagnostic..?
        }

        GPIO_INACTIVE(led_channel_red  );
        GPIO_INACTIVE(led_channel_green);
        GPIO_INACTIVE(led_channel_blue );

        current_flags &= ~current_diagnostic; // Acknowledge the completion of the diagnostic.

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
        // Reset the ESP32 for a bit...

        GPIO_ACTIVE(esp32_reset);
        FREERTOS_delay_ms(10);


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        // Reawaken the ESP32!

        FREERTOS_delay_ms(10);
        GPIO_INACTIVE(esp32_reset);



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
                }

                pool.log_entries[i].solarboard_A  = GPIO_SPINLOCK_ANALOG_READ(solarboard_analog_A) * SOLARBOARD_ANALOG_FACTOR;
                pool.log_entries[i].solarboard_B  = GPIO_SPINLOCK_ANALOG_READ(solarboard_analog_B) * SOLARBOARD_ANALOG_FACTOR;
                pool.log_entries[i].timer_event_1 = GPIO_READ(logic_timer_event_1);



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            struct MainFlightComputerDebugPacket packet =
                {
                    .timestamp_us           = TIMEKEEPING_microseconds(),
                    .solarboard_voltages[0] = GPIO_SPINLOCK_ANALOG_READ(solarboard_analog_A) * SOLARBOARD_ANALOG_FACTOR,
                    .solarboard_voltages[1] = GPIO_SPINLOCK_ANALOG_READ(solarboard_analog_B) * SOLARBOARD_ANALOG_FACTOR,
                    .flags                  =
                        (
                            (!!esp32_good                    ) << MainFlightComputerDebugStatusFlag_esp32   |
                            (!!lora_good                     ) << MainFlightComputerDebugStatusFlag_lora    |
                            (!!logger_good                   ) << MainFlightComputerDebugStatusFlag_logger  |
                            (!!GPIO_READ(logic_timer_event_1)) << MainFlightComputerDebugStatusFlag_te1     |
                            (!!vehicle_docked                ) << MainFlightComputerDebugStatusFlag_vehicle
                        ),
                };
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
